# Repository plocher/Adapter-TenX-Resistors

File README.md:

# Adapter-TenX-Resistors
## License: Creative Commons Attribution-NonCommercial-ShareAlike

Experimental current limited output expansion board adapter for MRCS cpNode evolution

initial version

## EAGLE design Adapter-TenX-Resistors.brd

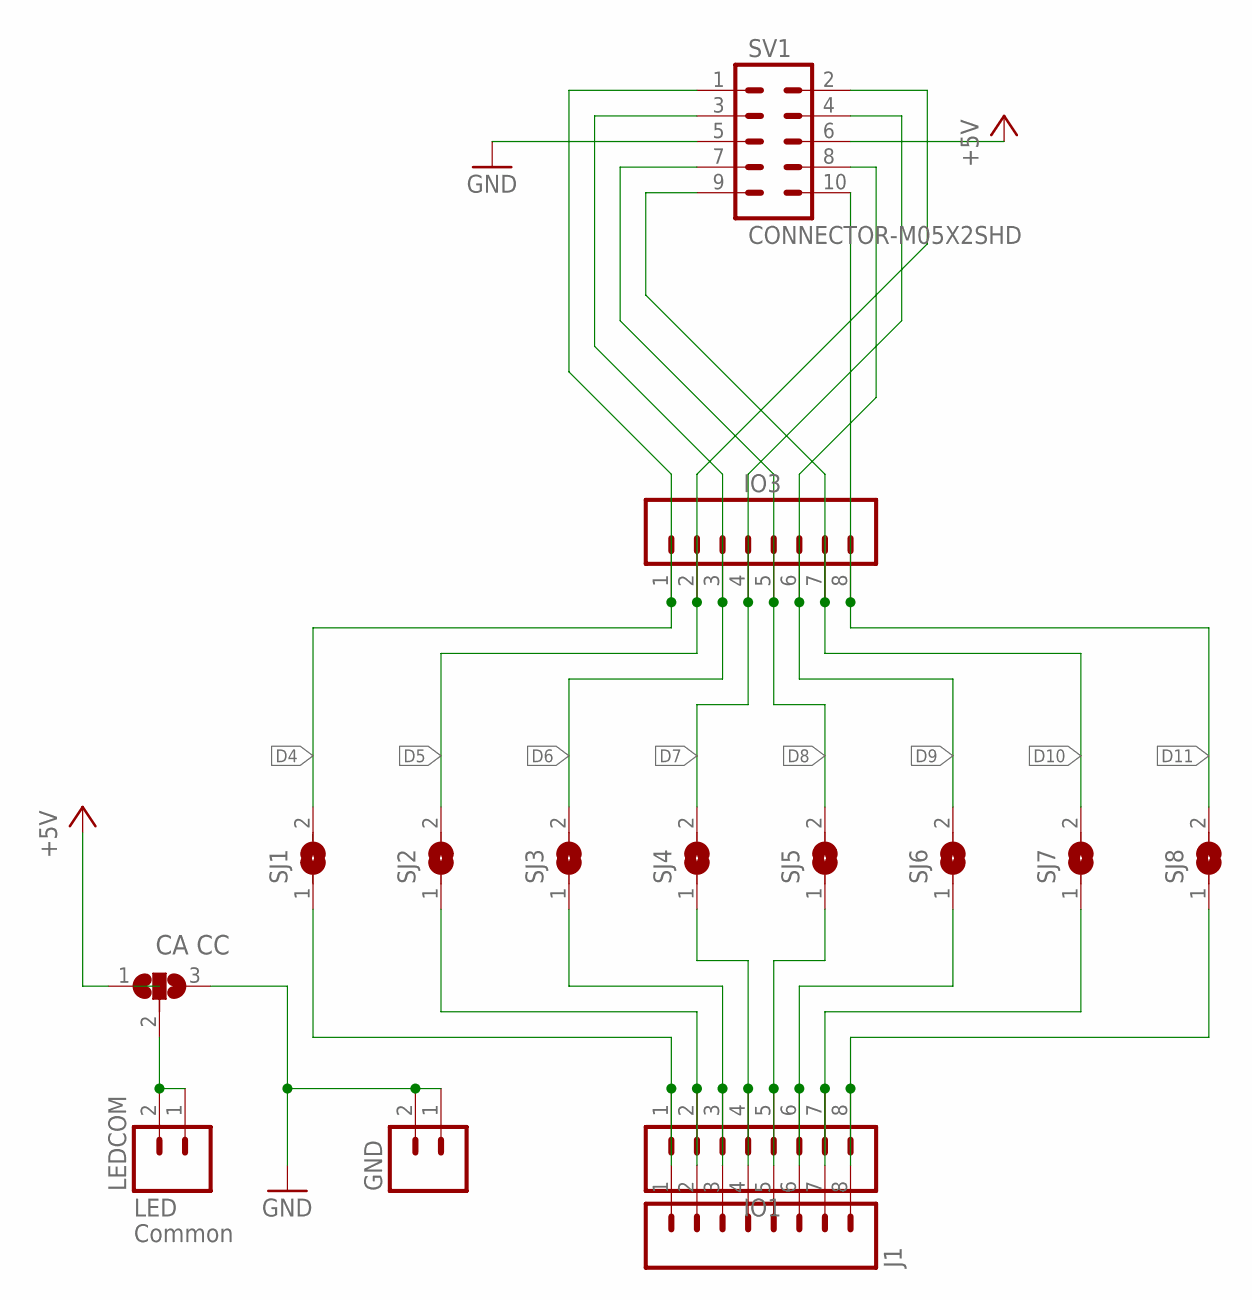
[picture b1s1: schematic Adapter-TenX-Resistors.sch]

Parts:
GND: M02POLAR_LOCK; MOLEX-1X2_LOCK
IO1, IO3: M081X08; 1X08
J1: CONNECTOR-M08LOCK_LONGPADS; 1X08_LOCK_LONGPADS
LEDCOM: M02POLAR_LOCK; MOLEX-1X2_LOCK
P1: CA CC; 3P-SMD-2X4.8
SJ1, SJ2, SJ3, SJ4, SJ5, SJ6, SJ7, SJ8: SJ
SV1: CONNECTOR-M05X2SHD; 2X5-SHROUDED

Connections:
+5V: P1.1, SV1.6
D4: IO3.1, SJ1.2, SV1.1
D5: IO3.2, SJ2.2, SV1.2
D6: IO3.3, SJ3.2, SV1.3
D7: IO3.4, SJ4.2, SV1.4
D8: IO3.5, SJ5.2, SV1.7
D9: IO3.6, SJ6.2, SV1.8
D10: IO3.7, SJ7.2, SV1.9
D11: IO3.8, SJ8.2, SV1.10
GND: GND.1, GND.2, P1.3, SV1.5
unnamed: IO1.1, J1.1, SJ1.1
unnamed: IO1.2, J1.2, SJ2.1
unnamed: IO1.3, J1.3, SJ3.1
unnamed: IO1.4, J1.4, SJ4.1
unnamed: IO1.5, J1.5, SJ5.1
unnamed: IO1.6, J1.6, SJ6.1
unnamed: IO1.7, J1.7, SJ7.1
unnamed: IO1.8, J1.8, SJ8.1
unnamed: LEDCOM.1, LEDCOM.2, P1.2

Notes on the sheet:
LED
Common

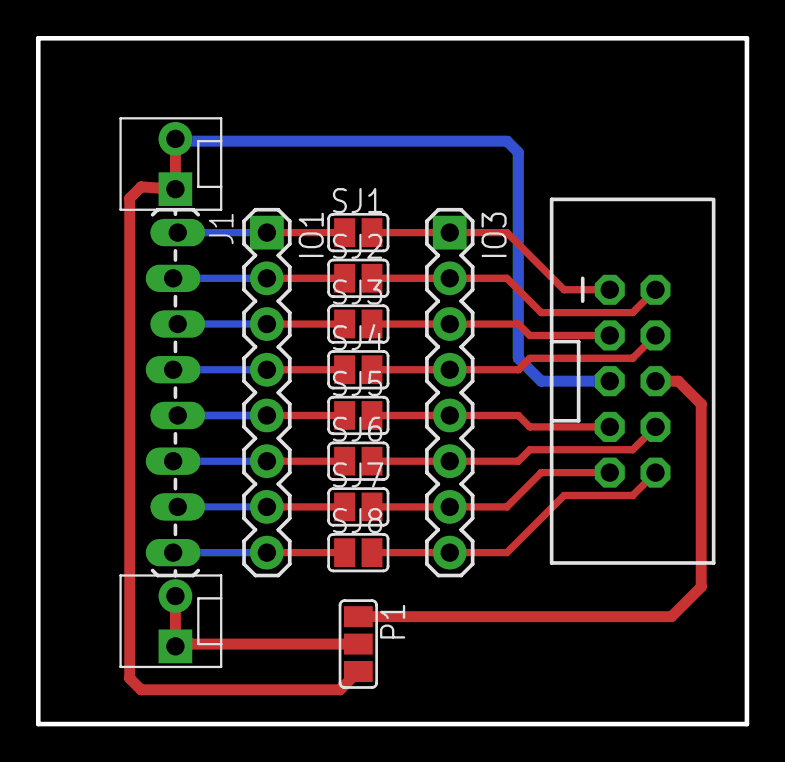
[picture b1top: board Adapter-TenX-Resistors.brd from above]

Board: 2 copper layers, 39.4 x 38.1 mm, 15 parts (0 on the bottom side), 19 nets.

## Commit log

2020-05-04 updated tags
